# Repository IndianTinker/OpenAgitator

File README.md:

OpenAgitator
============

http://wp.me/p1C1sd-7Q

The support files for making your own OpenAgitator.

It includes the firmware files for MSP430 compiled in CCS on windows.
The hardware files are included which include the schematic and board layout designed in Eagle 6.4 and hence 
are not compatible with lower versions.

Happy Tinkering!

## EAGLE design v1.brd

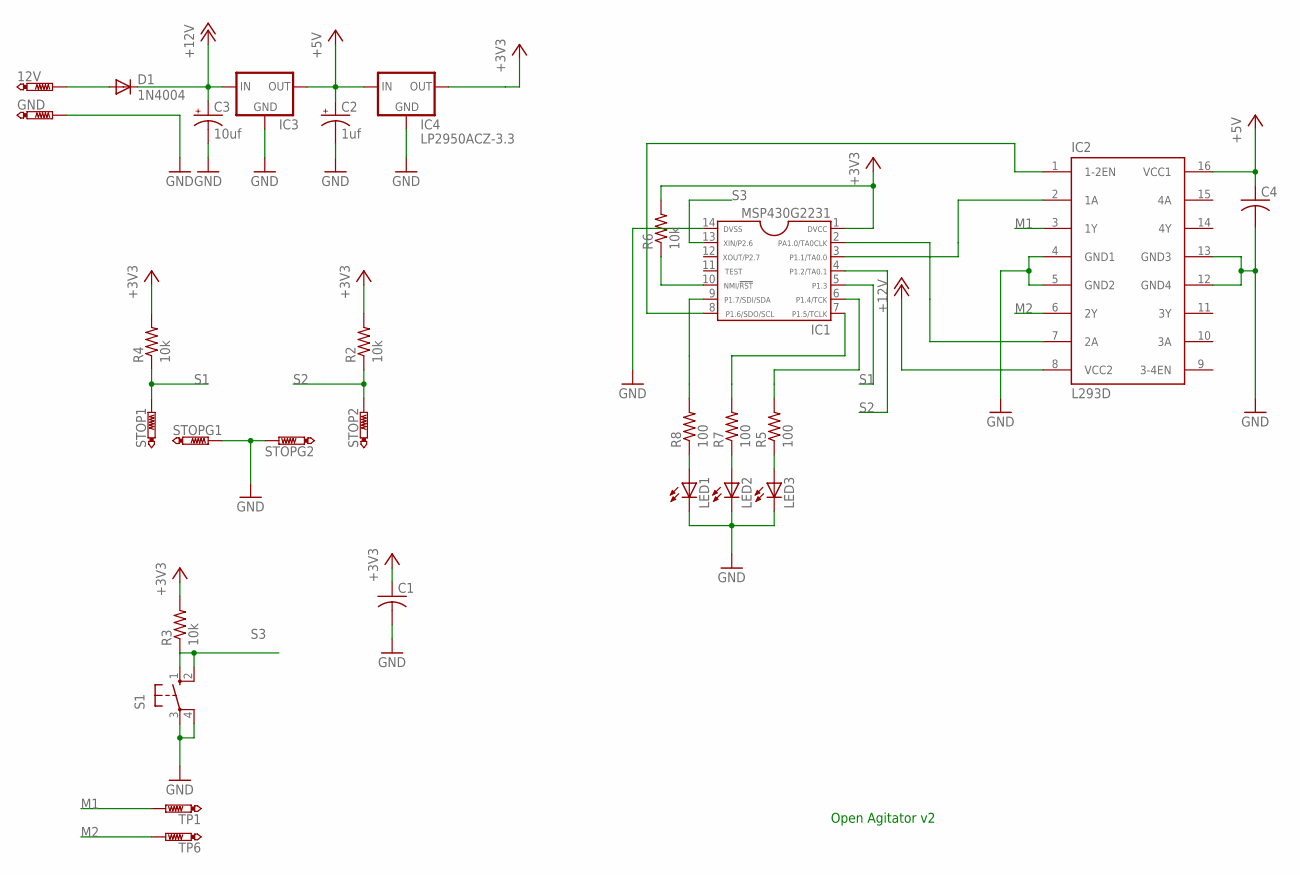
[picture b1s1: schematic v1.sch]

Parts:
12V: PTR1PAD1-13Y; P1-13Y
C1, C4: CAP0805; C0805
C2: 1uf; E2,5-6E
C3: 10uf; E2,5-6E
D1: 1N4004; DO41-10
GND: PTR1PAD1-13Y; P1-13Y
IC1: MSP430G2231; DIP14
IC2: L293D; DIL16
IC3: V_REG_78XX-TO-220; TO-220-ALT
IC4: LP2950ACZ-3.3; TO92
LED1, LED2, LED3: LED5MM
R2: 10k; 0207/10
R3, R4, R6: 10k; 0207/7
R5, R7: 100; 0207/7
R8: 100; 0207/10
S1: 10-XX; B3F-10XX
STOP1, STOP2: PTR1PAD1-13Y; P1-13Y
STOPG1, STOPG2: PTR1PAD1-13Y; P1-13Y
TP1, TP6: PTR1PAD1-13Y; P1-13Y

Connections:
+3V3: C1.1, IC1.1, IC4.1 (OUT), R2.2, R3.2, R4.2, R6.2
+5V: C2.+, C4.1, IC2.16 (VCC1), IC3.OUT, IC4.3 (IN)
+12V: C3.+, D1.C, IC2.8 (VCC2), IC3.IN
GND: C1.2, C2.-, C3.-, C4.2, GND.TP, IC1.14, IC2.4 (GND1), IC2.5 (GND2), IC2.12 (GND4), IC2.13 (GND3), IC3.GND, IC4.2 (GND), LED1.K (C), LED2.K (C), LED3.K (C), S1.3, S1.4 (P1), STOPG1.TP, STOPG2.TP
M1: IC2.3 (1Y), TP1.TP
M2: IC2.6 (2Y), TP6.TP
unnamed: IC1.8, IC2.1 (1-2EN)
unnamed: IC1.3, IC2.2 (1A)
unnamed: 12V.TP, D1.A
unnamed: IC1.2, IC2.7 (2A)
unnamed: IC1.10, R6.1
unnamed: IC1.7, R7.2
unnamed: IC1.6, R5.2
unnamed: IC1.9, R8.2
unnamed: LED1.A, R8.1
unnamed: LED2.A, R7.1
unnamed: LED3.A, R5.1
S1: IC1.5, R4.1, STOP1.TP
S2: IC1.4, R2.1, STOP2.TP
S3: IC1.13, R3.1, S1.1 (S), S1.2 (S1)

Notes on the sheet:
Open Agitator v2

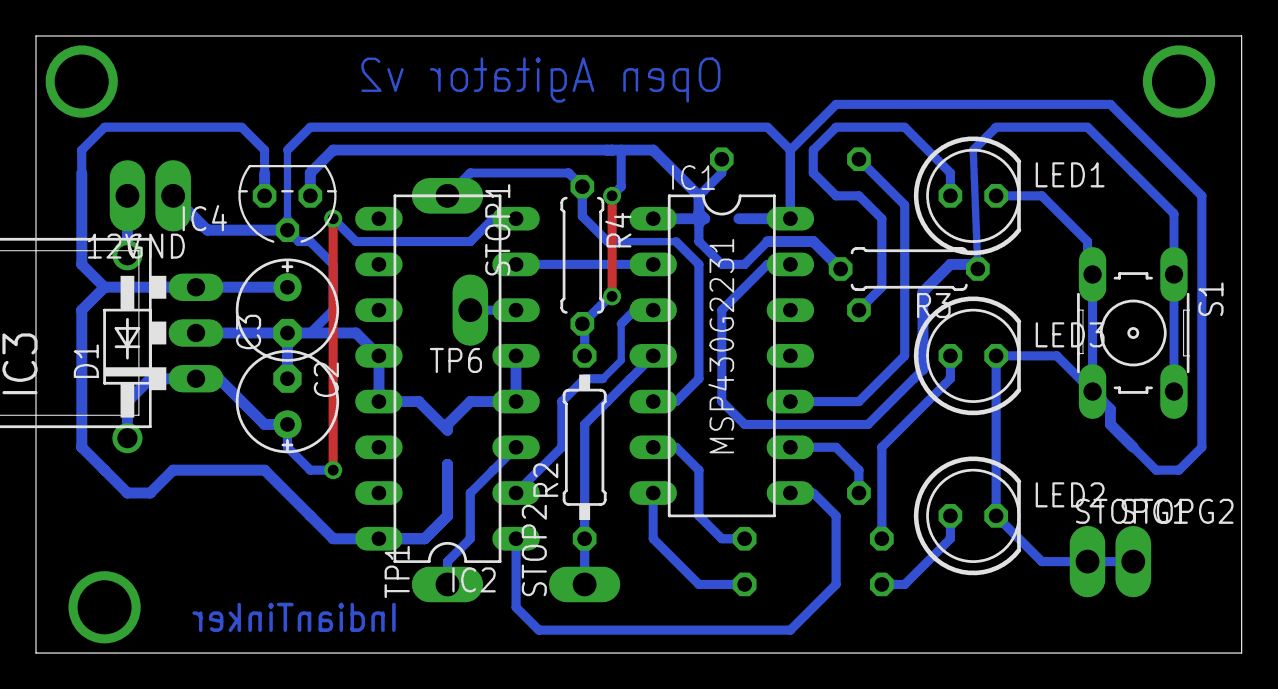
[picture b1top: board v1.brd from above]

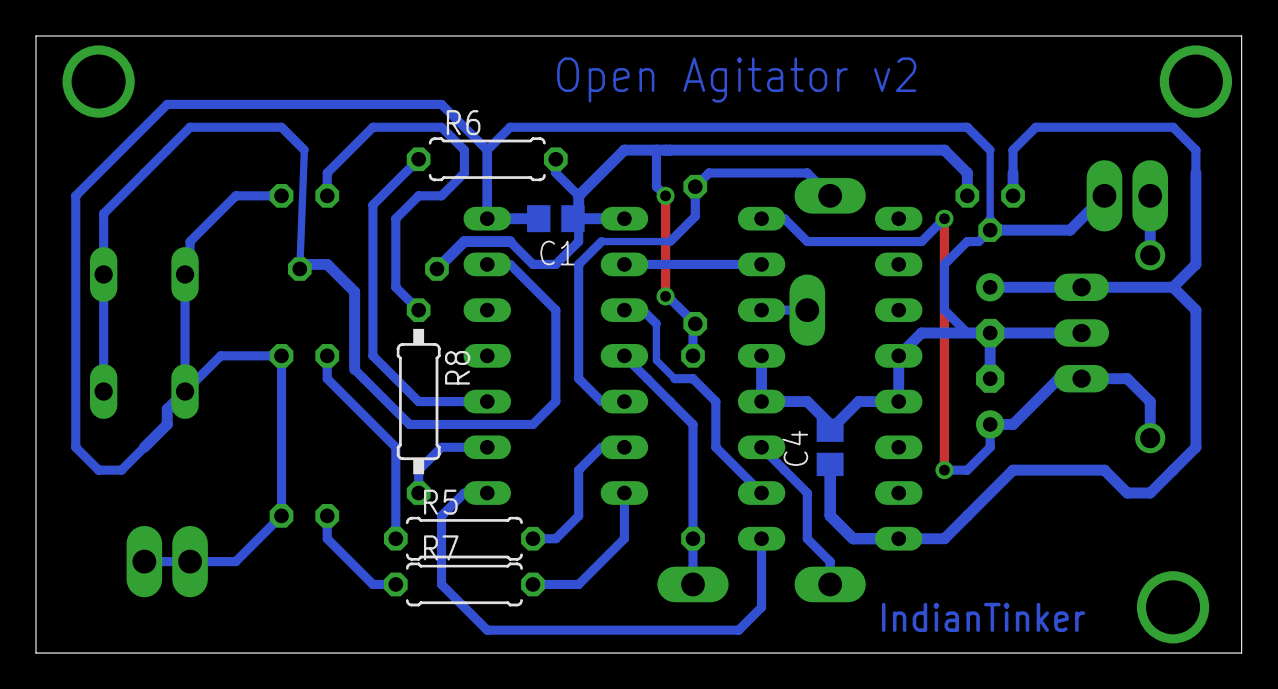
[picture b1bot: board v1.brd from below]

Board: 2 copper layers, 67.0 x 34.3 mm, 28 parts (6 on the bottom side), 20 nets.

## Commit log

2013-09-04 Files added
    Software folder has the firmware that is well commented.
    The eagle files are also included

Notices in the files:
parts and their libraries:
SparkFun: Licensing: CC v3.0 Share-Alike You are welcome to use this library for commercial purposes.
